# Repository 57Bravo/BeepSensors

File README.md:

# BeepBerry Sensors Carrier

Integrates UBlox GPS, IMU/MAG, BARO, and buzzer.

REV: - was built and verified on a BeepBerry, however, there are some problems with it:
* During integration, I blew the TPS61030 boost converter IC. I ordered a couple from Mouser and was able to replace it, fixing the device. I was not able to identify what caused the failure in that IC though.
* The buzzer isn't very loud, but can be used as a generic audio device. It's kind of neat that you can use espeak to do text to speech on such a small piezo.
* The GPS antenna doesn't have a large enough ground plane, so 3D fixes break often. It's still usable, just not what you'd expect from a UBlox devkit.
* GPS acquisition eats the battery, but you can control the GPS reset line to disable it to save power. 

## Using the buzzer

### Simple Tones
```
import RPi.GPIO as GPIO
import time
import random

GPIO.setmode(GPIO.BCM)
GPIO.setup(13, GPIO.OUT)

pwm = GPIO.PWM(13, 57)
pwm.start(10)

for i in range(random.randint(0,10)):
  pwm.ChangeFrequency(random.randint(1,10000))
  time.sleep(random.random())
pwm.stop()
```

### ALSA

In `/boot/config.txt`, add:

```
dtoverlay=audremap,enable_jack=on
dtoverlay=pwm-2chan,pin2=13,func2=4
```

then use anything that uses a sound card, IE:

`espeak "SAY SOMETHING"`

`aplay "some.wav"`

## Using GPS PPS

In `/boot/config.txt`, add:

`dtoverlay=pps-gpio,gpiopin=16`

This will allow you to use gpsd with `/dev/pps0`.

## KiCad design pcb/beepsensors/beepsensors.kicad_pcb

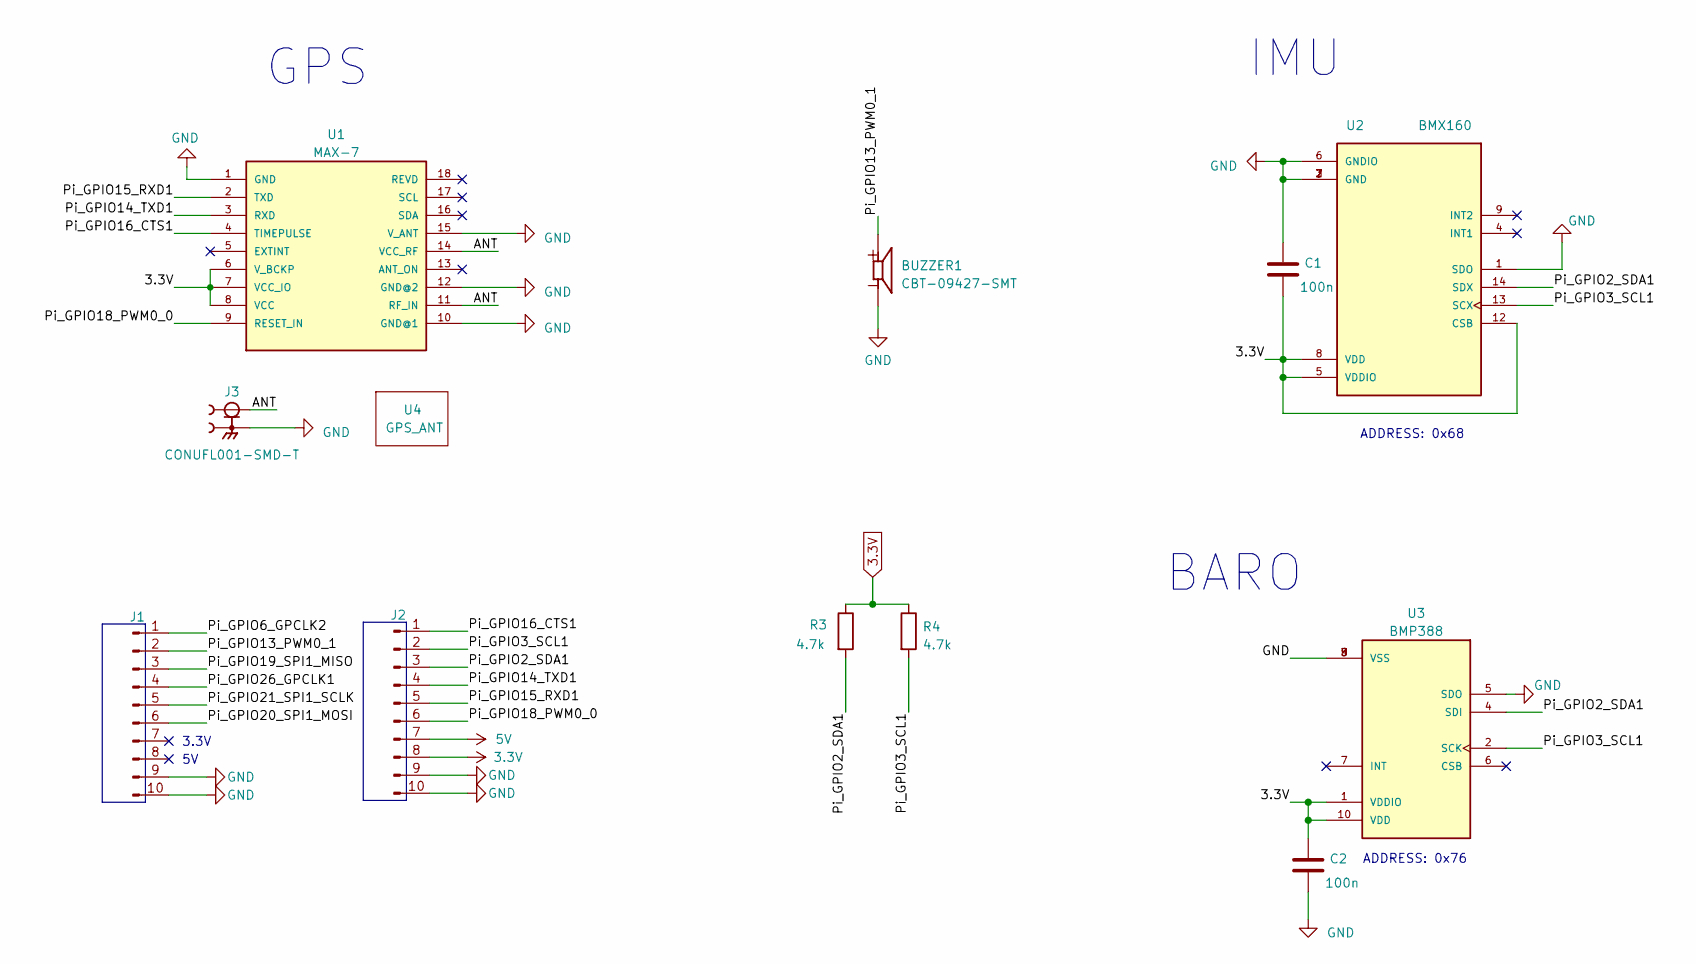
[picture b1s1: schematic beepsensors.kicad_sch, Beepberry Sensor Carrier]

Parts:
BUZZER1: CBT-09427-SMT; CUI_CBT-09427-SMT
C1, C2: 100n; C_0603_1608Metric
J1, J2: Conn_01x10_Pin; PinHeader_1x10_P2.54mm_Vertical
J3: CONUFL001-SMD-T; LINX_CONUFL001-SMD-T; PARTREV B
R3, R4: 4.7k; R_0603_1608Metric
U1: MAX-7; GPS18P-SMD-1.1-10X9.6MM; MPN MAX-7Q-0
U2: BMX160; PQFN50P250X300X100-14N; PARTREV 1.2
U3: BMP388; PQFN50P200X200X80-10N; PARTREV 1.1
U4: GPS_ANT; gps_ant

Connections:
3.3V: C1.2, C2.1, J2.8, R3.1, R4.1, U1.6 (V_BCKP), U1.7 (VCC_IO), U1.8 (VCC), U2.5 (VDDIO), U2.8 (VDD), U2.12 (CSB), U3.1 (VDDIO), U3.10 (VDD)
5V: J2.7
/ANT: J3.1, U1.11 (RF_IN), U1.14 (VCC_RF)
/Pi_GPIO2_SDA1: J2.3, R3.2, U2.14 (SDX), U3.4 (SDI)
/Pi_GPIO3_SCL1: J2.2, R4.2, U2.13 (SCX), U3.2 (SCK)
/Pi_GPIO6_GPCLK2: J1.1
/Pi_GPIO13_PWM0_1: BUZZER1.P, J1.2
/Pi_GPIO14_TXD1: J2.4, U1.3 (RXD)
/Pi_GPIO15_RXD1: J2.5, U1.2 (TXD)
/Pi_GPIO16_CTS1: J2.1, U1.4 (TIMEPULSE)
/Pi_GPIO18_PWM0_0: J2.6, U1.9 (RESET_IN)
/Pi_GPIO19_SPI1_MISO: J1.3
/Pi_GPIO20_SPI1_MOSI: J1.6
/Pi_GPIO21_SPI1_SCLK: J1.5
/Pi_GPIO26_GPCLK1: J1.4
GND: BUZZER1.M, C1.1, C2.2, J1.9, J1.10, J2.9, J2.10, J3.2, J3.3, U1.1 (GND), U1.10 (GND@1), U1.12 (GND@2), U1.15 (V_ANT), U2.1 (SDO), U2.2 (GND), U2.3 (GND), U2.6 (GNDIO), U2.7 (GND), U3.3 (VSS), U3.5 (SDO), U3.8 (VSS), U3.9 (VSS)

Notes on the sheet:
ADDRESS: 0x76
BARO
ADDRESS: 0x68
IMU
3.3V
GPS

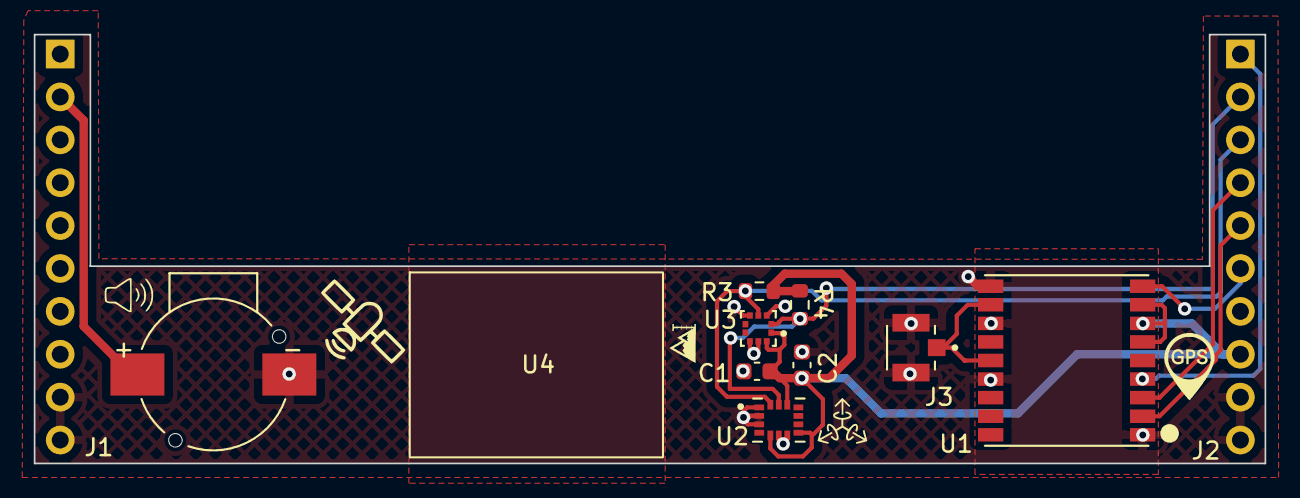
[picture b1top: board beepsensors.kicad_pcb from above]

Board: 2 copper layers, 72.9 x 25.4 mm, 12 parts (0 on the bottom side), 10 nets.

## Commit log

2023-07-10 export for GitHub
2023-07-10 added images
2023-07-25 add image of populated board
2023-07-27 added photos of board installed
2023-08-06 added some notes on using the buzzer for audio
2023-08-06 added some useful scripts
2023-08-06 notes on PPS
